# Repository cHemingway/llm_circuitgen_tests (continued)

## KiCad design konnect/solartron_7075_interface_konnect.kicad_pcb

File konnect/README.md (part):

# Konnect implementation

Solartron 7075 interface designed with [Konnect](https://github.com/mixelpixx/Konnect)
0.13.0, an MCP server that drives KiCad 10.0.6 (live IPC to the open editors,
with file-level tools for libraries and the schematic).

## Design

- 74 × 74 mm two-layer board. J1, a vertical DD-50 male (CAX DP-G-50P-ZC-YCLS,
  LCSC C54573066), sits on the bottom face, plugs into the meter's SKB socket
  and holds the board by its jackscrews. J2, a vertical USB-B (TE 5787834-1),
  sits on the top face.
- Meter side (GND_ISO): five SN74LVC165A shift registers read the 50-way
  interface's BCD and status lines through 100k pull-down networks. Two
  74LVC595A drive the command lines. An AMS1117-3.3 powers this side from a
  B0505S-1WR3 isolated DC-DC module.
- Isolation: six TLP2361 optocouplers carry the SPI-style links across a
  copper-free band about 4.8 mm wide. No net crosses the barrier.
- USB side (GND): RP2354A (internal flash), AP2112K-3.3, USBLC6-2SC6, BOOTSEL
  and RUN buttons, and an SWD header.
- Parts: KiCad's libraries, with LCSC numbers for every fitted part (the SWD
  header is optional and has none). KiCad has no DD-50, so its symbol and
  footprint are in the project library. The footprint follows the CAX
  part's drawing, checked against the DIN 41652 dimensions in Harting's
  catalogue. The project library also has a TLP2361 symbol with an
  inverting output.
- ERC: 0 errors, 0 warnings. DRC: 0 unconnected items and one cosmetic
  error: C17 pad 2 on the USB side, a ground pad with one thermal spoke
  where KiCad wants two, as in the first layout. The remaining items are
  warnings: footprints that differ from their library copies, silkscreen
  clipping, overlap and clearance, and a missing LCSC footprint field on the
  parity check.

## Review 1: pin swapping

The shift-register and resistor-array pins were re-assigned to untangle the
meter-side routing. The '165 inputs (D0–D7) are equivalent, as are the
'595 outputs (QA–QH) and the elements of the 100k arrays. The swaps were
therefore made both within each part and between identical parts.

- Each resistor array feeds one side of one '165. The 36 DVM outputs are
  taken in D-sub pin order, left to right. So the tracks run D-sub pin →
  array → '165 pin without crossing, almost all on the top layer.
- The '595 outputs follow the order of their D-sub pins. QA, the pin on the
  far side of the chip, takes the outermost signal.
- U16 D3..D0 keep the 0,0,1,1 signature. The SAMPLE line moved from U18
  QE/QD to QA/QC. The schematic's serial-link note now carries the full bit
  map that the firmware needs.
- The '165 LOAD and clock pins (1 and 2) escape to vias above each chip and
  join on two bottom-layer buses. Ground "pockets" (a bar and via over each
  array's ground pads, and vias for '165 pins 8 and 15) were placed before
  routing, so the input bus routes around them.
- The meter side was re-routed with Freerouting on top of those fixed
  pieces. The USB side was re-imported unchanged.

| Meter side | Before | After |
| --- | --- | --- |
| 36 '165 input nets | 1,343 mm, 53 vias | 781 mm, 7 vias |
| 13 '595 output nets | 157 mm, 7 vias | 118 mm, 1 via |
| 14 other nets (LOAD/SCK/MOSI/MISO, chain, +3V3_ISO) | 874 mm, 51 vias | 793 mm, 47 vias |
| All meter-side signals | 2,374 mm, 111 vias | 1,692 mm, 55 vias |
| GND_ISO stitching | 43 vias, 154 mm | 34 vias, 81 mm |

Whole board: 1,660 → 1,275 track segments and 201 → 136 vias.
`fab/routing_before_after.png` compares the meter-side routing before and after.

## Review 3: moving parts

The meter-side parts were moved, and the pins re-assigned again to suit.
This includes the swaps between parts offered in reply to review 2. The 36
DVM input tracks were laid out by a script, in one repeated pattern,
instead of by the autorouter.

- U16, the '165 with only four DVM inputs, moved from the middle of the row
  to the right-hand end. The nine '165 input sides that carry DVM lines now
  sit side by side, 11.08 mm per chip, which is twice the pitch of the
  D-sub's groups of four pins.
- Each array sits directly under its four D-sub pins, turned so that its
  signal pads face the connector. The tracks drop straight into the pads.
  On the way out, the outer two leave from the ends of the array, and the
  inner two run between its two rows of pads to the ends. Each '165 side
  takes two tracks from outside the chip and two from under the chip body.
- All 36 input tracks are on the top layer except DD-50 pin 36, which sits
  directly above pin 3. It uses one bottom-layer track and a via.
- The '165 decoupling caps moved to the top of each chip, between its two
  sets of input tracks, with a via to a bottom-layer +3V3_ISO spine. C29
  moved above the regulator to make room for U16. U19 turned round so that
  PRINT_LEVEL reaches its input directly.
- Both shift-register chains now run in board order. MOSI enters U18, U18
  feeds U17, and U17 loops back into U16. The '165 chain runs U16 → U15 →
  U14 → U12 → U13 → MISO. CMD_RATIO_N moved to U18 QD, next to the other
  U18 outputs. The serial-link note in the schematic has the new bit map.
- The script also placed:
  - the LOAD, SCK and OE buses on the bottom layer under both '595s, with a
    riser down the left of the D-sub;
  - SCK down a free channel under U15;
  - SIPO_CH1 under the '595 bodies;
  - a +3V3_ISO rail along the top edge and another along the opto row;
  - SIPO_LOOP down the right-hand side;
  - the '165 chain and MISO in a channel under the chips.
- Freerouting routed the rest: MOSI, the '595 outputs and the opto links.
  The USB side is unchanged.

| Meter side | Review 1 | Review 3 |
| --- | --- | --- |
| 36 '165 input nets | 781 mm, 7 vias | 655 mm, 1 via |
| 13 '595 output nets | 118 mm, 1 via | 96 mm, 0 vias |
| 14 other nets (LOAD/SCK/MOSI/MISO, chain, +3V3_ISO) | 793 mm, 47 vias | 807 mm, 35 vias |
| All meter-side signals | 1,692 mm, 55 vias | 1,558 mm, 36 vias |
| GND_ISO stitching | 34 vias, 81 mm | 27 vias, 65 mm |

Whole board: 1,275 → 958 track segments and 136 → 110 vias. DRC lost
Review 1's three starved thermals on the meter side (C24, C30 and C31). It
gained eight silkscreen overlap warnings, where the moved caps' reference
text overlaps the '165 outlines and C37's overlaps U19. Konnect has no tool
to move reference text. The positions file was regenerated; the BOM is
unchanged. `fab/routing_review3.png` compares the meter-side routing after
Review 1 and now.

| Path | Contents |
| --- | --- |
| `solartron_7075_interface_konnect.kicad_sch` / `.kicad_pcb` / `.kicad_pro` | KiCad project |
| `solartron.kicad_sym`, `solartron.pretty/` | Project symbols and footprints, including rect-pad copies of the stock footprints |
| `fab/` | Gerbers and drill files, JLCPCB BOM and positions, `schematic.pdf`, `pcb_layers.pdf`, DRC report, render, routing comparisons for reviews 1 and 3 |
| `CONVERSATION.md` | Session log and statistics |
| `stats.py`, `calls.csv` | Script for the statistics, and every API call with its category |
| `REVIEW_CONVERSATION.md` | Review log and statistics |
| `review_stats.py`, `review_calls.csv` | Script for the review statistics and log, and every review API call with its category |

## Notes on the tool

- Konnect's Specctra (Freerouting) export refuses roundrect pads, duplicate
  pad numbers and bottom-side footprints. Nearly every KiCad SMD footprint
  has roundrect pads. 15 stock footprints were therefore copied into the
  project library with rectangular pads. Routing-only variants were swapped
  in for the export and swapped back after the import: renumbered duplicate
  pads, and a front-side mirror of the bottom-mounted DD-50.
- The DSN export wrote each pin's rotation as an absolute angle, not relative
  to the footprint, so rotated parts had their pads turned twice and
  Freerouting reported 226 violations. The pin rotations were corrected in
  the scratch copy of the DSN. The session import then refused one part
  because the angles were written as 270 and −90, so those angles were
  normalised.
- Konnect has no tool to delete or move a via, or to delete a copper zone,
  and it deletes tracks one segment at a time. Its SES import also needs a
  board with no tracks, vias or zones. So re-routing after the pin swaps
  needed KiCad's own Edit ▸ Global Deletions, run in the GUI by screen
  control with the user's agreement. In Review 3 the same dialog was driven
  through the menu bar in the background. Each time, the whole board's
  copper was then re-imported through Konnect: the USB side unchanged, the
  meter side new.
- Konnect can move and rotate footprints but not their reference text, so
  silkscreen overlaps from moved parts stay as DRC warnings.
- KiCad's save rewrites the project's design rules and net classes, so the
  rules were re-applied before each DRC.
- The ground pours needed a lot of manual work: stitching vias, a
  ground-only Freerouting pass, a small grid router written in the
  scratchpad, and hand-placed thermal spokes.
- Freerouting 2.4.1 was downloaded with the user's permission and run both
  through Konnect and from the command line.

## Session statistics

`stats.py` reads the session transcript,
`~/.claude/projects/-Users-chris-repos-llm-circuitgen-tests/47e5c69c-808f-4cd7-8f0d-34a4d53529bd.jsonl`.
It takes everything before the export request (2026-10-15 18:44:30 UTC),
prints the tables in `CONVERSATION.md` and writes `calls.csv`. The export
itself ran in a resumed session, `3539381d-…`, whose file starts with a copy
of the original's later records. The original file is the complete record.

The review that followed ran in the same resumed session. `review_stats.py`
reads that session's transcript from the first review comment to the review
export request. It prints the review tables, writes `review_calls.csv` and,
with `--write-md`, writes `REVIEW_CONVERSATION.md`. The resumed session
writes no cost-state records, so the review figures come from the
transcript's per-response usage and tool timings, priced at the published
Opus 5.5 prices. `REVIEW_CONVERSATION.md` explains how each figure was
measured.

- **Totals** (tokens, API time, tool time and cost) come from the last
  `cost-state` record before the export request. API calls are the 520
  distinct assistant message ids; the usage-limit error message is not a
  call.
- **Active time** is measured from each typed message until the reply
  finished, giving four stretches.
  - Waiting for the user's answers to the two AskUserQuestion prompts (27 s
    and 2 min 14 s) is left out.
  - The 4 min stall between 20:52 and 20:57 on 2026-10-14 is left out. The
    session stopped after a tool result with no reply, and nothing ran
    until the user's "keep going".
  - Time waiting on background autorouter runs counts as active.
  - Each call is credited from its request (the record that triggered it)
    to the next call's request in the same stretch. The last call runs to
    the end of the stretch.
  - The 80 s compaction goes under Not attributable.
- **Categories** are set by call number in `stats.py`. Judgement calls:
  - The DD-50 footprint work (calls 43 and 68–71) is PCB. The search for a
    DD-50 drawing that came before it is Schematic & research, as part
    selection.
  - Everything from the schematic-to-PCB update (call 153) to the
    fabrication outputs (call 515) is PCB. That includes:
    - the rect-pad footprint copies, and pointing the schematic symbols at
      them;
    - the short replies to autorouter progress notifications;
    - the BOM export with the Gerbers.
  - Other covers:
    - creating the branch (call 1);
    - the two commits, the file send and the two summaries;
    - the connector status checks after "Continue" (calls 195–196).
- **Prices.** There are only two distinct cost-state snapshots, too few for
  a least-squares fit, so the published prices are used. They come from
  <https://platform.claude.com/docs/en/about-claude/pricing>, read on
  2026-10-15.
  - Claude Opus 5.5, per million tokens: $4 input, $5 for 5-minute cache
    writes, $8 for 1-hour cache writes, $0.20 for cache reads and $20 for
    output. The full 1M context is at standard prices.
  - Claude Haiku 5.5 (the web-tool helper): $0.10 input and $0.50 output for
    prompts up to 100k tokens, plus $10 per 1,000 web searches.

  Every cache write the transcript logs is a 1-hour write, and the 5-minute
  and 1-hour writes are priced separately per call. Checked against the
  snapshots:

  | Snapshot | Model | Reported | Published prices |
  | --- | --- | --- | --- |
  | 2026-10-14 21:05 | Opus 5.5 | $35.5377 | $35.5377 |
  | 2026-10-14 21:05 | Haiku 5.5 | $0.0777 | $0.0777 |
  | 2026-10-15 12:31 | Opus 5.5 | $112.1028 | $112.1034 |
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
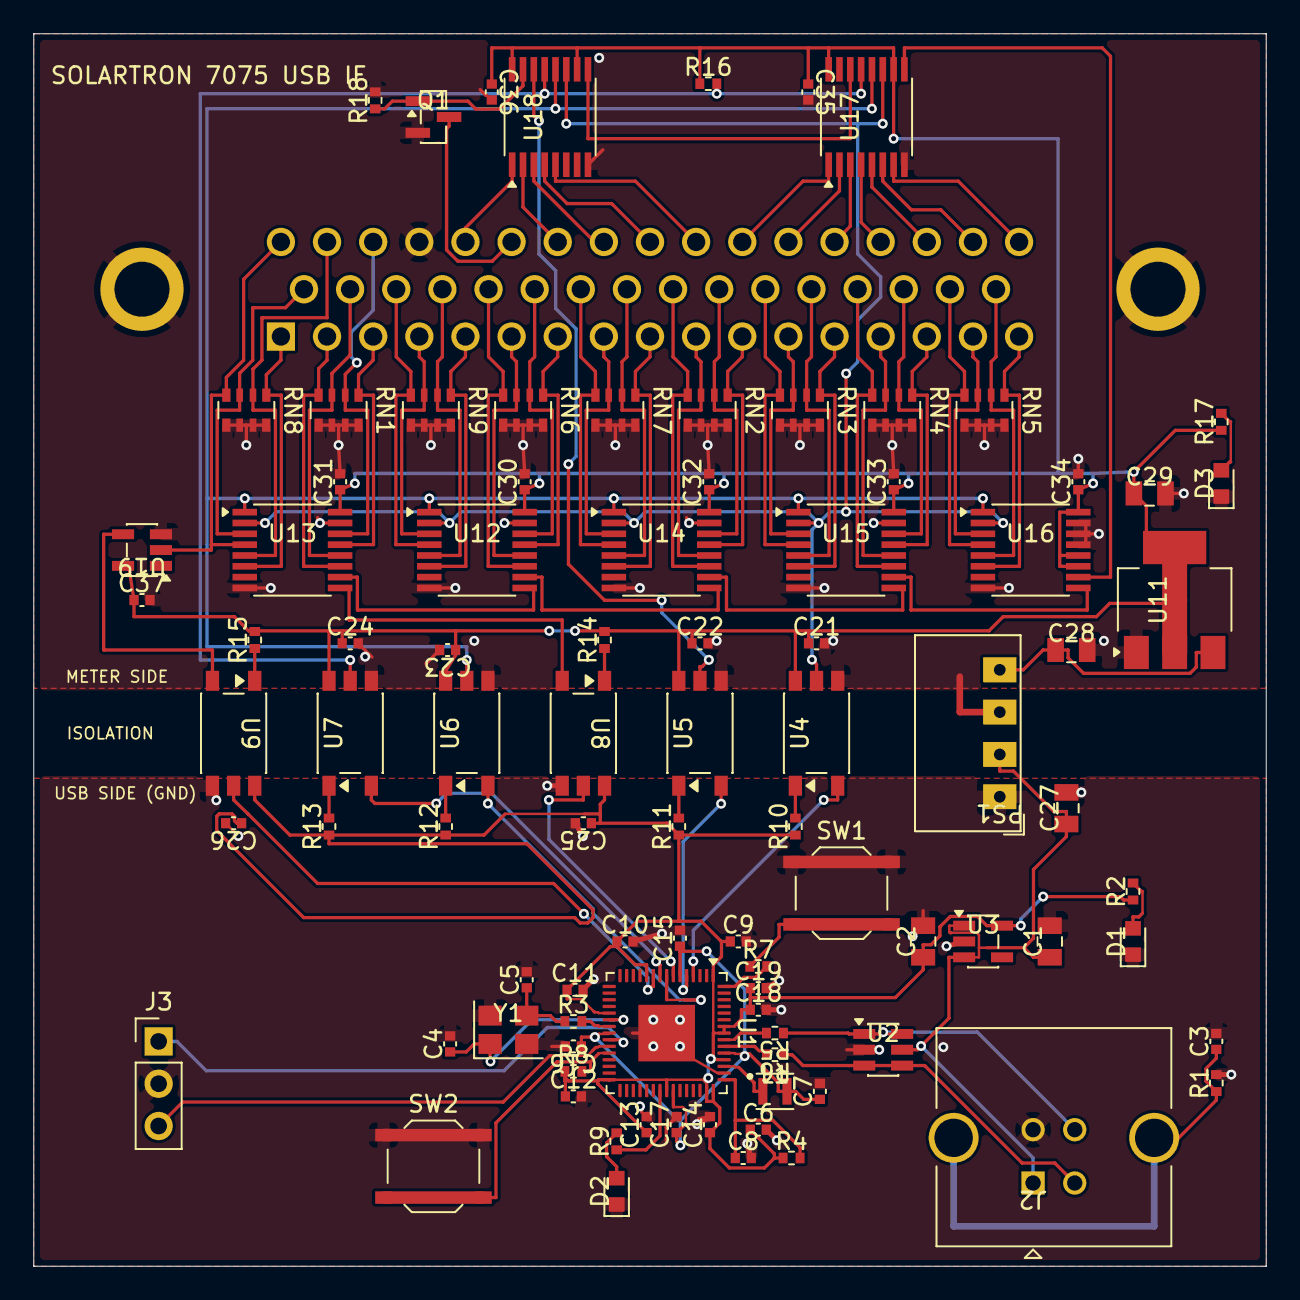
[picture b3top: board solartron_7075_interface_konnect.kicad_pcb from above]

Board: 2 copper layers, 74.0 x 74.0 mm, 93 parts (1 on the bottom side), 100 nets.

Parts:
C1, C2, C27, C28: 10uF; C_0805_2012Metric_RectPads
C3: 4.7nF; C_0402_1005Metric_RectPads
C4, C5: 15pF; C_0402_1005Metric_RectPads
C6, C7, C8: 4.7uF; C_0402_1005Metric_RectPads
C9, C10, C11, C12, C13, C14, C15, C16, C17, C18, C19, C21, C22, C23, C24, C25, C26, C30, C31, C32, C33, C34, C35, C36, C37: 100nF; C_0402_1005Metric_RectPads
C29: 22uF; C_0805_2012Metric_RectPads
D1, D2, D3: RED; LED_0603_1608Metric_RectPads
J1: DD-50 Male (Solartron SKB); DSUB-50_Pins_Vertical_P2.77x2.84mm_MountingHoles
J2: USB_B; USB_B_TE_5787834_Vertical_RectPads
J3: SWD; PinHeader_1x03_P2.54mm_Vertical
L1: 3.3uH; L_Murata_DFE201610P_RectPads
PS1: B0505S-1WR3; Converter_DCDC_Murata_CRE1xxxxxxSC_THT_RectPads
Q1: 2N7002; SOT-23_RectPads
R1: 1M; R_0402_1005Metric_RectPads
R2, R3, R7, R9, R17: 1k; R_0402_1005Metric_RectPads
R4: 33; R_0402_1005Metric_RectPads
R5, R6: 27; R_0402_1005Metric_RectPads
R8, R16: 10k; R_0402_1005Metric_RectPads
R10, R11, R12, R13, R14, R15: 470; R_0402_1005Metric_RectPads
R18: 100k; R_0402_1005Metric_RectPads
RN1, RN2, RN3, RN4, RN5, RN6, RN7, RN8, RN9: 100k; R_Array_Convex_4x0603
SW1: BOOTSEL; SW_Push_1P1T_XKB_TS-1187A
SW2: RUN; SW_Push_1P1T_XKB_TS-1187A
U1: RP2354A; QFN-60-1EP_7x7mm_P0.4mm_EP3.4x3.4mm
U2: USBLC6-2SC6; SOT-23-6_RectPads
U3: AP2112K-3.3; SOT-23-5_RectPads
U4, U5, U6, U7, U8, U9: TLP2361; SO-5-6_4.55x3.7mm_P1.27mm_RectPads
U11: AMS1117-3.3; SOT-223-3_TabPin2_RectPads
U12, U13, U14, U15, U16: SN74LVC165APWR; TSSOP-16_4.4x5mm_P0.65mm_RectPads
U17, U18: 74LVC595APW; TSSOP-16_4.4x5mm_P0.65mm_RectPads
U19: 74LVC1G17; SOT-23-5_RectPads
Y1: 12MHz; Crystal_SMD_3225-4Pin_3.2x2.5mm_RectPads

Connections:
+3V3: C2.1, C6.1, C9.1, C10.1, C11.1, C12.1, C13.1, C14.1, C18.1, C19.1, C25.1, C26.1, R2.1, R4.1, R8.1, R10.1, R11.1, R12.1, R13.1, U1.1, U1.11, U1.20, U1.30, U1.38, U1.44, U1.45, U1.49, U1.53, U1.54, U3.5, U8.6, U9.6
+3V3_ISO: C21.1, C22.1, C23.1, C24.1, C29.1, C30.1, C31.1, C32.1, C33.1, C34.1, C35.1, C36.1, C37.1, R14.2, R15.2, R16.1, R17.1, U4.6, U5.6, U6.6, U7.6, U11.2, U12.16, U13.16, U14.16, U15.16, U16.11, U16.12, U16.16, U17.10, U17.16, U18.10, U18.16, U19.5
+5V_ISO: C28.1, PS1.4, U11.3
/+1V1: C7.1, C15.1, C16.1, C17.1, L1.2, U1.6, U1.23, U1.39, U1.50
/BCD0_1: J1.25, RN7.2, U14.5
/BCD0_2: J1.24, RN7.4, U14.4
/BCD0_4: J1.23, RN6.2, U12.14
/BCD0_8: J1.22, RN6.4, U12.11
/BCD1_1: J1.21, RN9.2, U12.5
/BCD1_2: J1.20, RN9.4, U12.4
/BCD1_4: J1.19, RN1.3, U13.12
/BCD1_8: J1.18, RN8.3, U13.3
/BCD2_1: J1.17, RN5.1, U16.6
/BCD2_2: J1.16, RN5.3, U16.3
/BCD2_4: J1.15, RN4.1, U15.13
/BCD2_8: J1.14, RN4.3, U15.12
/BCD3_1: J1.13, RN3.1, U15.6
/BCD3_2: J1.12, RN3.3, U15.3
/BCD3_4: J1.11, RN2.1, U14.13
/BCD3_8: J1.10, RN2.3, U14.12
/BCD4_1: J1.9, RN7.1, U14.6
/BCD4_2: J1.8, RN7.3, U14.3
/BCD4_4: J1.7, RN6.1, U12.13
/BCD4_8: J1.6, RN6.3, U12.12
/BCD5_1: J1.5, RN9.1, U12.6
/BCD5_2: J1.4, RN9.3, U12.3
/BCD5_4: J1.3, RN1.1, U13.13
/BCD5_8: J1.2, RN1.4, U13.11
/BCD6_1: J1.1, RN8.1, U13.6
/CMD_AUTORANGE_INH: J1.47, U17.4
/CMD_FN_42: J1.42, U18.4
/CMD_FN_43: J1.43, U18.5
/CMD_FPL_N: J1.38, U18.1
/CMD_INT_1: J1.46, U17.3
/CMD_INT_2: J1.45, U17.2
/CMD_INT_4: J1.44, U17.1
/CMD_RATIO_N: J1.41, U18.3
/CMD_RNG_1: J1.48, U17.5
/CMD_RNG_2: J1.49, U17.6
/CMD_RNG_4: J1.50, U17.7
/CMD_SAMPLE_CONTACT: J1.39, Q1.3
/CMD_SAMPLE_PULSE: J1.40, U18.2
/DATA_CAN_CHANGE: J1.35, RN8.2, U13.5
/FN_OUT_28: J1.28, RN3.4, U15.4
/FN_OUT_29: J1.29, RN3.2, U15.5
/ISO_LOAD: U6.5, U12.1, U13.1, U14.1, U15.1, U16.1, U17.12, U18.12
/ISO_MISO: U8.3, U13.9
/ISO_MOSI: U5.5, U18.14
/ISO_OE_N: R16.2, U7.5, U17.13, U18.13
/ISO_PRINT_DRV: U9.3, U19.4
/ISO_SCK: U4.5, U12.2, U13.2, U14.2, U15.2, U16.2, U17.11, U18.11
/LED_STAT: R9.1, U1.37
/MISO: U1.7, U8.5
/OPTO_LOAD: U1.8, U6.3
/OPTO_MOSI: U1.5, U5.3
/OPTO_OE_N: U1.9, U7.3
/OPTO_SCK: U1.4, U4.3
/OVERLOAD: J1.36, RN1.2, U13.14
/PISO_CH1: U12.9, U13.10
/PISO_CH2: U12.10, U14.9
/PISO_CH3: U14.10, U15.9
/PISO_CH4: U15.10, U16.9
/POL_NEG: J1.27, RN2.2, U14.14
/POL_POS: J1.26, RN2.4, U14.11
/PRINT: U1.10, U9.5
/PRINT_LEVEL: J1.34, RN8.4, U13.4, U19.2
/PRINT_PULSE: J1.33, RN5.2, U16.5
/RNG_OUT_1: J1.32, RN5.4, U16.4
/RNG_OUT_2: J1.31, RN4.2, U15.14
/RNG_OUT_4: J1.30, RN4.4, U15.11
/SAMPLE_CONTACT_DRV: Q1.1, R18.1, U18.15
/SIPO_CH1: U17.14, U18.9
/SIPO_LOOP: U16.10, U17.9
/SWCLK: J3.1, U1.24
/SWDIO: J3.3, U1.25
/USB_CONN_DM: J2.2, R6.1, U2.3, U2.4
/USB_CONN_DP: J2.3, R5.1, U2.1, U2.6
/USB_DM: R6.2, U1.51
/USB_DP: R5.2, U1.52
/USB_SHIELD: C3.1, J2.SH, R1.1
/VREG_AVDD: C8.1, R4.2, U1.46
/VREG_LX: L1.1, U1.48
/XIN: C4.1, U1.21, Y1.1
/XTAL_OUT: C5.1, R3.1, Y1.3
GND: C1.2, C2.2, C3.2, C4.2, C5.2, C6.2, C7.2, C8.2, C9.2, C10.2, C11.2, C12.2, C13.2, C14.2, C15.2, C16.2, C17.2, C18.2, C19.2, C25.2, C26.2, C27.2, D1.1, D2.1, J2.4, J3.2, PS1.1, R1.2, SW1.1, SW2.1, U1.47, U1.61, U2.2, U3.2, U8.4, U9.4, Y1.2, Y1.4
GND_ISO: C21.2, C22.2, C23.2, C24.2, C28.2, C29.2, C30.2, C31.2, C32.2, C33.2, C34.2, C35.2, C36.2, C37.2, D3.1, J1.37, J1.SH, PS1.3, Q1.2, R18.2, RN1.5, RN1.6, RN1.7, RN1.8, RN2.5, RN2.6, RN2.7, RN2.8, RN3.5, RN3.6, RN3.7, RN3.8, RN4.5, RN4.6, RN4.7, RN4.8, RN5.5, RN5.6, RN5.7, RN5.8, RN6.5, RN6.6, RN6.7, RN6.8, RN7.5, RN7.6, RN7.7, RN7.8, RN8.5, RN8.6, RN8.7, RN8.8, RN9.5, RN9.6, RN9.7, RN9.8, U4.4, U5.4, U6.4, U7.4, U11.1, U12.8, U12.15, U13.8, U13.15, U14.8, U14.15, U15.8, U15.15, U16.8, U16.13, U16.14, U16.15, U17.8, U18.8, U19.3
unnamed: D1.2, R2.2
unnamed: D2.2, R9.2
unnamed: D3.2, R17.2
unnamed: R7.1, SW1.2
unnamed: R8.2, SW2.2, U1.26
unnamed: R3.2, U1.22
unnamed: R7.2, U1.60
unnamed: R10.2, U4.1
unnamed: R11.2, U5.1
unnamed: R12.2, U6.1
unnamed: R13.2, U7.1
unnamed: R14.1, U8.1
unnamed: R15.1, U9.1
VBUS: C1.1, C27.1, J2.1, PS1.2, U2.5, U3.1, U3.3

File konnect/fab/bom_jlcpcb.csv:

"Comment","Designator","Footprint","LCSC Part #","MPN","Manufacturer","Quantity"
"10uF","C1,C2,C27,C28","solartron:C_0805_2012Metric_RectPads","C15850","CL21A106KAYNNNE","Samsung Electro-Mechanics","4"
"4.7nF","C3","solartron:C_0402_1005Metric_RectPads","C1538","0402B472K500NT","FH (Guangdong Fenghua)","1"
"15pF","C4,C5","solartron:C_0402_1005Metric_RectPads","C1548","0402CG150J500NT","FH (Guangdong Fenghua)","2"
"4.7uF","C6-C8","solartron:C_0402_1005Metric_RectPads","C23733","CL05A475MP5NRNC","Samsung Electro-Mechanics","3"
"100nF","C9-C19,C21-C26,C30-C37","solartron:C_0402_1005Metric_RectPads","C1525","CL05B104KO5NNNC","Samsung Electro-Mechanics","25"
"22uF","C29","solartron:C_0805_2012Metric_RectPads","C45783","CL21A226MAQNNNE","Samsung Electro-Mechanics","1"
"RED","D1-D3","solartron:LED_0603_1608Metric_RectPads","C2286","KT-0603R","Hubei KENTO Elec","3"
"DD-50 Male (Solartron SKB)","J1","solartron:DSUB-50_Pins_Vertical_P2.77x2.84mm_MountingHoles","C54573066","DP-G-50P-ZC-YCLS","CAX (Zhejiang Chuangdu)","1"
"USB_B","J2","solartron:USB_B_TE_5787834_Vertical_RectPads","C592900","5787834-1","TE Connectivity","1"
"SWD","J3","Connector_PinHeader_2.54mm:PinHeader_1x03_P2.54mm_Vertical","","2.54mm 1x3 pin header (fit by hand / optional)","","1"
"3.3uH","L1","solartron:L_Murata_DFE201610P_RectPads","C42411119","AOTA-B201610S3R3-101-T","Abracon","1"
"B0505S-1WR3","PS1","solartron:Converter_DCDC_Murata_CRE1xxxxxxSC_THT_RectPads","C7465178","B0505S-1WR3","EVISUN","1"
"2N7002","Q1","solartron:SOT-23_RectPads","C8545","2N7002","Jiangsu Changjing (CJ)","1"
"1M","R1","solartron:R_0402_1005Metric_RectPads","C26083","0402WGF1004TCE","UNI-ROYAL","1"
"1k","R2,R3,R7,R9,R17","solartron:R_0402_1005Metric_RectPads","C11702","0402WGF1001TCE","UNI-ROYAL","5"
"33","R4","solartron:R_0402_1005Metric_RectPads","C25105","0402WGF330JTCE","UNI-ROYAL","1"
"27","R5,R6","solartron:R_0402_1005Metric_RectPads","C25100","0402WGF270JTCE","UNI-ROYAL","2"
"10k","R8,R16","solartron:R_0402_1005Metric_RectPads","C25744","0402WGF1002TCE","UNI-ROYAL","2"
"470","R10-R15","solartron:R_0402_1005Metric_RectPads","C25117","0402WGF4700TCE","UNI-ROYAL","6"
"100k","R18","solartron:R_0402_1005Metric_RectPads","C25741","0402WGF1003TCE","UNI-ROYAL","1"
"100k","RN1-RN9","Resistor_SMD:R_Array_Convex_4x0603","C1996","4D03WGJ0104T5E","UNI-ROYAL","9"
"BOOTSEL","SW1","Button_Switch_SMD:SW_Push_1P1T_XKB_TS-1187A","C318884","TS-1187A-B-A-B","XKB Connection","1"
"RUN","SW2","Button_Switch_SMD:SW_Push_1P1T_XKB_TS-1187A","C318884","TS-1187A-B-A-B","XKB Connection","1"
"RP2354A","U1","Package_DFN_QFN:QFN-60-1EP_7x7mm_P0.4mm_EP3.4x3.4mm","C41378174","RP2354A","Raspberry Pi","1"
"USBLC6-2SC6","U2","solartron:SOT-23-6_RectPads","C7519","USBLC6-2SC6","STMicroelectronics","1"
"AP2112K-3.3","U3","solartron:SOT-23-5_RectPads","C51118","AP2112K-3.3TRG1","Diodes Incorporated","1"
"TLP2361","U4-U9","solartron:SO-5-6_4.55x3.7mm_P1.27mm_RectPads","C107626","TLP2361(TPL,E","Toshiba","6"
"AMS1117-3.3","U11","solartron:SOT-223-3_TabPin2_RectPads","C6186","AMS1117-3.3","Advanced Monolithic Systems","1"
"SN74LVC165APWR","U12-U16","solartron:TSSOP-16_4.4x5mm_P0.65mm_RectPads","C41558098","SN74LVC165APWR","Texas Instruments","5"
"74LVC595APW","U17,U18","solartron:TSSOP-16_4.4x5mm_P0.65mm_RectPads","C426713","74LVC595APW,118","Nexperia","2"
"74LVC1G17","U19","solartron:SOT-23-5_RectPads","C7836","SN74LVC1G17DBVR","Texas Instruments","1"
"12MHz","Y1","solartron:Crystal_SMD_3225-4Pin_3.2x2.5mm_RectPads","C20625731","ABM8-272-T3","Abracon","1"

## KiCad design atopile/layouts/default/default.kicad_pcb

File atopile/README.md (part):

# Solartron 7075 USB interface (atopile)

An RP2354A USB interface that plugs straight into the 50-way SKB socket of a
Solartron 7075 DVM fitted with the 70754 Parallel BCD Interface Unit (service
manual, section 9). Every signal to and from the meter crosses an optical
isolation barrier, so USB ground noise never reaches the meter's ground. SKB
pin 37 is the meter's earth and logic 0.

Designed with atopile 0.15.9 (`ato build`). The parts come from atopile's
package library where it had them, and from LCSC otherwise.

## Architecture

```
 USB side (GND)                         |  DVM side (GND_ISO)
                                        |
 USB-B (vertical) -> 500 mA PTC, USBLC6 |
   +5V --+--> TLV75901 -> +3V3          |
         +--> IB0505LS-1WR3 ===========>|==> +5V_ISO (regulated, 1.5 kV)
                                        |
 RP2354A  GPIO18 SCK  --> TLP2361 ======|==> SCK_ISO   -> 5x 74HCT165 CP, 2x 74HCT595 SHCP
          GPIO19 MOSI --> TLP2361 ======|==> MOSI_ISO  -> first 74HCT595 DS
          GPIO17 LATCH--> TLP2361 ======|==> LATCH_ISO -> 74HCT165 /PL, 74HCT595 STCP
          GPIO20 OE_N --> TLP2361 ======|==> OE_N_ISO  -> 74HCT595 /OE (10 k pull-up)
          GPIO16 MISO <-- TLP2361 ======|<== first 74HCT165 Q7
          GPIO21 DRDY <-- TLP2361 ======|<== 74AHCT1G125 <- SKB 34 (PRINT level)
                                        |
                                        |   SKB 1-36  (BCD, polarity, function, range,
                                        |              print, data-can-change, overload)
                                        |              -> 5x 74HCT165 (40-bit chain)
                                        |   SKB 38, 40-50 <- 2x 74HCT595 (16-bit chain)
                                        |   SKB 39 (contact SAMPLE) <- 2N7002 to pin 37
```

* Only six logic signals cross the barrier. Each goes through a Toshiba
  TLP2361 optocoupler (15 MBd, 80 ns max delay). Every channel is
  non-inverting: the MCU or HCT output sinks the LED cathode, and the anode
  is fed from 330 Ω (3.3 V side) or 680 Ω (5 V side), about 4.5 mA.
* The DVM side uses HCT logic at 5 V because the 7075's outputs are TTL
  levels: a '1' is +2.4 to +6 V from a 6 kΩ source. The 74HCT595 outputs
  sink 6 mA at under 0.33 V, which meets the 7075 input spec of under 0.5 V
  at 5 mA.
* **Safe at reset.** While the MCU is in reset or not yet configured, its
  GPIOs are Hi-Z, so the opto LEDs are off and every isolated line idles
  high. That keeps `OE_N_ISO` high, so the 595 outputs stay Hi-Z and the
  meter's command inputs sit at its own pull-ups, exactly as if nothing were
  connected. Manual §9, diagram 9.2 (70754 board 2) confirms the pull-ups:
  * every command input has 4.7 kΩ to +5 V into 74-series TTL, so Hi-Z reads
    '1' = inactive (no lockout, no ratio, DC, 10 s, autorange; the manual's
    "REMOTE with nothing connected" state)
  * CONTACT SAMPLE has 2.2 kΩ to +5 V, so with the MOSFET off there is no
    sample
  * PULSE SAMPLE is AC-coupled (47 kΩ + 22 nF), so only a rising edge
    triggers it
* The four spare 74HCT165 inputs are tied to two 1s and two 0s, so firmware
  can detect a broken link or a missing isolated supply. Their places in the
  frame are in the read-frame table below.

## Firmware interface

SPI0 runs in mode 0 at 1 MHz or less. The limit comes from the round trip
through two optos, about 200 ns. **LATCH must be driven as a plain GPIO**, not
as the SPI chip select, because the 74HCT165s are held in load mode while it
is low. Set GPIO17–20 to 8 mA drive.

One transaction:

1. Pulse LATCH (GPIO17) low for at least 1 µs, then return it high. The
   rising edge does two things: the 165s capture the DVM outputs, and the
   595s present the command word that was shifted in last time.
2. Exchange 5 bytes over SPI. MOSI = `00 00 00 CMD_HI CMD_LO`. MISO = 5
   status bytes.
3. To apply the new command now, pulse LATCH again. Otherwise it is applied
   at the next transaction.
4. After the first valid command has been latched, drive OE_N (GPIO20) low.
   That command must have the PULSE SAMPLE bit = 0. PULSE SAMPLE is
   AC-coupled in the meter, so enabling the outputs with that bit = 1 would be
   a rising edge and would trigger a sample.

DRDY (GPIO21) follows SKB pin 34, PRINT level. It goes high when a reading is
complete and the outputs have been updated.

<!-- BEGIN bit maps: generated by scripts/pin_swap.py -->
### Read frame (MISO, MSB first)

Each cell gives the SKB pin and its meaning. `1`/`0` are the link-check
constants: firmware should check them on every read.

| Byte | bit7 | bit6 | bit5 | bit4 | bit3 | bit2 | bit1 | bit0 |
|---|---|---|---|---|---|---|---|---|
| 0 | 1 1×10⁶ | 34 PRINT level | 2 8×10⁵ | 18 8×10¹ | `0` | `1` | `0` | 35 DATA CAN CHANGE |
| 1 | 19 4×10¹ | 3 4×10⁵ | 36 OVERLOAD | 20 2×10¹ | 22 8×10⁰ | 5 1×10⁵ | 21 1×10¹ | 4 2×10⁵ |
| 2 | 6 8×10⁴ | 23 4×10⁰ | 7 4×10⁴ | 24 2×10⁰ | `1` | 9 1×10⁴ | 25 1×10⁰ | 8 2×10⁴ |
| 3 | 11 4×10³ | 27 −ve | 10 8×10³ | 26 +ve | 28 function A | 12 2×10³ | 29 function B | 13 1×10³ |
| 4 | 32 range (1) | 14 8×10² | 31 range (2) | 30 range (4) | 15 4×10² | 33 PRINT pulse | 16 2×10² | 17 1×10² |

### Command word (MOSI bytes 3–4, CMD_HI = bits 15–8)

| Bit | SKB pin | Signal (manual §9) |
|---|---|---|
| 0 | 38 | FRONT PANEL LOCKOUT (0 = locked out) |
| 1 | 39 | CONTACT SAMPLE (1 = MOSFET closes 39 to 37) |
| 2 | 43 | FUNCTION B |
| 3 | 42 | FUNCTION A |
| 4 | 44 | Integration time (4) |
| 5 | 41 | RATIO (0 = ratio) |
| 6 | 40 | PULSE SAMPLE (pulse high for more than 100 µs) |
| 7 | – | unused |
| 8 | 45 | Integration time (2) |
| 9 | 49 | Range (2) |
| 10 | 50 | Range (4) |
| 11 | 48 | Range (1) |
| 12 | 47 | AUTORANGE (1 = autorange inhibited, use the commanded range) |
| 13 | 46 | Integration time (1) |
| 14 | – | unused |
| 15 | – | unused |

* FUNCTION, read as (43, 42): 11 = DC, 01 = AC, 10 = Ω, 00 = CHECK.
* Integration time, read as (44, 45, 46) = (4)(2)(1): 011 = 1 ms, 100 = 20 ms,
  101 = 100 ms, 110 = 1 s, 111 = 10 s.
* Range, read as (50, 49, 48) = (4)(2)(1): 000 = 1000 V / 10 MΩ … 101 = 10 mV /
  100 Ω, 110 = auto / 10 Ω, 111 = auto.
<!-- END bit maps -->

Commands only take effect while the meter is in REMOTE. That means either the
REMOTE button is pressed, or the FRONT PANEL LOCKOUT bit = 0.

## Board

* 78 × 60 mm rectangle, 4 layers, 1.6 mm. It sits flat on the back of the
  meter and has no mounting holes.
* **Stack-up** (JLCPCB's standard 7628 build, nominal values):

  | Layer | Use | Copper | Dielectric below |
  |---|---|---|---|
  | F.Cu | signals, all parts except the DD-50 | 35 µm | 0.2 mm 7628 prepreg |
  | In1.Cu | ground planes: GND (USB half), GND_ISO (DVM half) | 17.5 µm | 1.065 mm core |
  | In2.Cu | supply planes: +3V3 (USB half), +5V_ISO (DVM half) | 17.5 µm | 0.2 mm 7628 prepreg |
  | B.Cu | signals, DD-50 | 35 µm | |

* **Bottom face:** Amphenol DD50P364TXLF, a vertical PCB-mount DD-50 plug. It
  mates with SKB and is held by 4-40 jackscrews through its 3.1 mm flange
  holes. The top face is kept clear within 4 mm of each jackscrew for the
  screw heads.
* **Top face:**
  * the vertical USB-B (SHOU HAN BF 180) and the rest of the components
  * isolation barrier along the board centreline: a 3.2 mm keep-out on all
    four layers with no tracks, vias or copper, crossed only by the six
    TLP2361s and the SIP DC-DC. The inner planes stop 1.9 mm either side of
    the centreline, so the planes on the two sides are 3.8 mm apart.
  * no pours on the outer layers; they are left for signals
* `scripts/place_components.py` produces the initial placement, the layer
  stack and the zones, using atopile's own `PCB_Transformer`.
  `scripts/check_layout.py` checks:
  * every pad is inside the outline
  * no footprints overlap
  * all USB-side pads are north of the barrier and all DVM-side pads south
  * the jackscrew keep-outs are clear
* The TLV75901 library module arrives pre-routed. The placement script moves
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
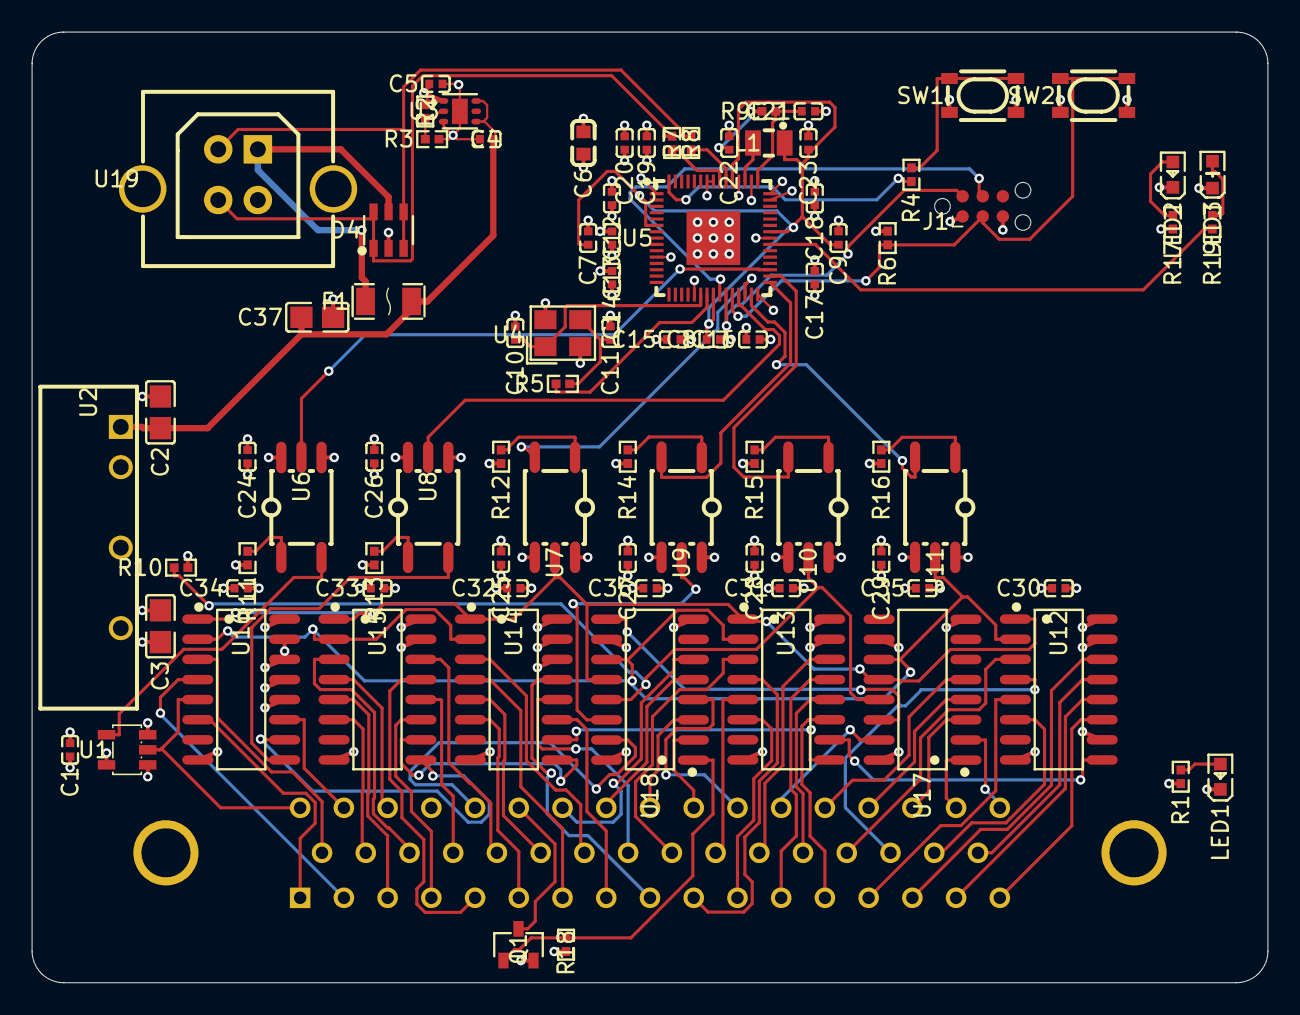
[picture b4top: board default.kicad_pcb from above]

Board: 4 copper layers, 78.0 x 60.0 mm, 86 parts (1 on the bottom side), 99 nets.

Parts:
C1, C7, C8, C9, C12, C13, C14, C15, C16, C17, C18, C19, C20, C24, C25, C26, C27, C28, C29, C30, C31, C32, C33, C34, C35, C36: 100nF ±10%; C0402
C2: 4.7µF ±10%; C0805
C3, C37: 10µF ±10%; C0805
C4, C5: 1µF ±10%; C0402
C6: 10µF ±10%; C0603
C10, C11: 15pF ±5%; C0402
C21, C22, C23: 4.7µF ±20%; C0402
CN1: CONN-TH_50P-P2.76_DD50P364TXLF
D4: SOT-23-6_L2.9-W1.6-P0.95-LS2.8-BL
F1: F1206
J1: Tag-Connect_TC2030-IDC-NL_2x03_P1.27mm_Vertical
L1: IND-SMD_L2.0-W1.6_AOTA-B201610S3R3-101-T
LED1, LED2: LED0603-RD
LED3: LED0603-R-RD
Q1: SOT-23-3_L2.9-W1.3-P1.90-LS2.4-BR
R1: 3.3kΩ ±1%; R0402
R2, R18: 100kΩ ±1%; R0402
R3: 20kΩ ±1%; R0402
R4, R5: 1kΩ ±1%; R0402
R6, R10: 10kΩ ±1%; R0402
R7, R8: 27Ω ±1%; R0402
R9: 33Ω ±1%; R0402
R11, R13: 680Ω ±1%; R0402
R12, R14, R15, R16: 330Ω ±1%; R0402
R17, R19: 1.5kΩ ±1%; R0402
SW1, SW2: KEY-SMD_4P-L4.2-W3.2-P2.20-LS4.6
U1: SOT-23-5_L3.0-W1.7-P0.95-LS2.8-BR
U2: PWRM-TH_BXXXXLS-1WR3
U3: WSON-6_L2.0-W2.0-P0.65-TL-EP
U4: CRYSTAL-SMD_4P-L3.2-W2.5-BL
U5: QFN-60_L7.0-W7.0-P0.40-TL-EP3.4
U6, U7, U8, U9, U10, U11: OPTO-SMD-5_L3.7-W4.6-P1.27-LS7.0-BR
U12, U13, U14, U15, U16, U17, U18: SOIC-16_L9.9-W3.9-P1.27-LS6.0-BL
U19: USB-B-TH_921-111A1010Y10201

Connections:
+1V1: C7.1, C8.1, C9.1, C23.1, L1.2, U5.6, U5.23, U5.39, U5.50
+3V3: C5.1, C6.1, C12.1, C13.1, C14.1, C15.1, C16.1, C17.1, C18.1, C19.1, C20.1, C22.1, C24.1, C26.1, J1.1, R2.1, R6.2, R9.1, R12.1, R14.1, R15.1, R16.1, R17.1, U3.1, U5.1, U5.11, U5.20, U5.30, U5.38, U5.44, U5.45, U5.49, U5.53, U5.54, U6.6, U8.6
+5V: C2.1, C4.1, C37.1, F1.2, U2.1, U3.4, U3.6
+5V_ISO: C1.1, C3.1, C25.1, C27.1, C28.1, C29.1, C30.1, C31.1, C32.1, C33.1, C34.1, C35.1, C36.1, R1.1, R10.2, R11.1, R13.1, U1.5, U2.6, U7.6, U9.6, U10.6, U11.6, U12.16, U13.16, U14.14, U14.16, U15.16, U16.13, U16.16, U17.10, U17.16, U18.10, U18.16
AN: R11.2, U6.1
BOOTSEL_SW: R4.2, SW1.1, SW1.2
CLK: J1.4, U5.24
DATA_N: D4.3, D4.4, R8.1, U19.2
DATA_P: D4.1, D4.6, R7.1, U19.3
DIO: J1.2, U5.25
DRDY: U5.33, U6.5
DRDY_ISO: U1.4, U6.3
GND: C2.2, C4.2, C5.2, C6.2, C7.2, C8.2, C9.2, C10.2, C11.2, C12.2, C13.2, C14.2, C15.2, C16.2, C17.2, C18.2, C19.2, C20.2, C21.2, C22.2, C23.2, C24.2, C26.2, C37.2, D4.2, J1.5, LED2.1, LED3.2, R3.2, SW1.3, SW1.4, SW2.3, SW2.4, U2.2, U3.3, U3.7, U4.2, U4.4, U5.47, U5.61, U6.4, U8.4, U19.4, U19.5, U19.6
GND_ISO: C1.2, C3.2, C25.2, C27.2, C28.2, C29.2, C30.2, C31.2, C32.2, C33.2, C34.2, C35.2, C36.2, CN1.37, CN1.S1, CN1.S2, LED1.1, Q1.2, R18.2, U1.1, U1.3, U2.4, U7.4, U9.4, U10.4, U11.4, U12.8, U12.10, U12.15, U13.8, U13.15, U14.8, U14.15, U15.8, U15.15, U16.8, U16.12, U16.14, U16.15, U17.8, U18.8
LATCH: U5.28, U7.3
LATCH_ISO: U7.5, U12.1, U13.1, U14.1, U15.1, U16.1, U17.12, U18.12
LDO_FB: R2.2, R3.1, U3.2
LED_ISO_A: LED1.2, R1.2
LED_PWR_A: LED2.2, R17.2
LED_STATUS_A: LED3.1, R19.2
MISO: U5.27, U8.5
MISO_ISO: U8.3, U16.9
MOSI: U5.31, U9.3
MOSI_ISO: U9.5, U18.14
N_RESET: J1.3, R6.1, SW2.1, SW2.2, U5.26
OE_N: U5.32, U10.3
OE_N_ISO: R10.1, U10.5, U17.13, U18.13
QSPI_SS: R4.1, U5.60
SAMPLE_CONTACT_GATE: Q1.1, R18.1, U18.1
SCK: U5.29, U11.3
SCK_ISO: U11.5, U12.2, U13.2, U14.2, U15.2, U16.2, U17.11, U18.11
SI_CHAIN_1: U15.9, U16.10
SI_CHAIN_2: U14.9, U15.10
SI_CHAIN_3: U13.9, U14.10
SI_CHAIN_4: U12.9, U13.10
SKB01_D6_1: CN1.1, U16.6
SKB02_D5_8: CN1.2, U16.4
SKB03_D5_4: CN1.3, U15.5
SKB04_D5_2: CN1.4, U15.11
SKB05_D5_1: CN1.5, U15.13
SKB06_D4_8: CN1.6, U14.6
SKB07_D4_4: CN1.7, U14.4
SKB08_D4_2: CN1.8, U14.11
SKB09_D4_1: CN1.9, U14.13
SKB10_D3_8: CN1.10, U13.4
SKB11_D3_4: CN1.11, U13.6
SKB12_D3_2: CN1.12, U13.13
SKB13_D3_1: CN1.13, U13.11
SKB14_D2_8: CN1.14, U12.5
SKB15_D2_4: CN1.15, U12.14
SKB16_D2_2: CN1.16, U12.12
SKB17_D2_1: CN1.17, U12.11
SKB18_D1_8: CN1.18, U16.3
SKB19_D1_4: CN1.19, U15.6
SKB20_D1_2: CN1.20, U15.3
SKB21_D1_1: CN1.21, U15.12
SKB22_D0_8: CN1.22, U15.14
SKB23_D0_4: CN1.23, U14.5
SKB24_D0_2: CN1.24, U14.3
SKB25_D0_1: CN1.25, U14.12
SKB26_POL_POS: CN1.26, U13.3
SKB27_POL_NEG: CN1.27, U13.5
SKB28_FUNC_OUT_A: CN1.28, U13.14
SKB29_FUNC_OUT_B: CN1.29, U13.12
SKB30_RANGE_OUT_4: CN1.30, U12.3
SKB31_RANGE_OUT_2: CN1.31, U12.4
SKB32_RANGE_OUT_1: CN1.32, U12.6
SKB33_PRINT_PULSE: CN1.33, U12.13
SKB34_PRINT_LEVEL: CN1.34, U1.2, U16.5
SKB35_DATA_CAN_CHANGE: CN1.35, U16.11
SKB36_OVERLOAD: CN1.36, U15.4
SKB38_LOCKOUT: CN1.38, U18.15
SKB39_SAMPLE_CONTACT: CN1.39, Q1.3
SKB40_SAMPLE_PULSE: CN1.40, U18.6
SKB41_RATIO: CN1.41, U18.5
SKB42_FUNC_CMD_A: CN1.42, U18.3
SKB43_FUNC_CMD_B: CN1.43, U18.2
SKB44_INT_TIME_4: CN1.44, U18.4
SKB45_INT_TIME_2: CN1.45, U17.15
SKB46_INT_TIME_1: CN1.46, U17.5
SKB47_AUTORANGE: CN1.47, U17.4
SKB48_RANGE_CMD_1: CN1.48, U17.3
SKB49_RANGE_CMD_2: CN1.49, U17.1
SKB50_RANGE_CMD_4: CN1.50, U17.2
SO_CHAIN_1: U17.14, U18.9
STATUS_LED: R19.1, U5.37
USB_DM: R8.2, U5.51
USB_DP: R7.2, U5.52
VBUS: D4.5, F1.1, U19.1
VREG_AVDD: C21.1, R9.2, U5.46
VREG_LX: L1.1, U5.48
XIN: C10.1, U4.1, U5.21
XOUT: R5.1, U5.22
XTAL_OUT: C11.1, R5.2, U4.3
opto_latch-AN: R12.2, U7.1
opto_miso-AN: R13.2, U8.1
opto_mosi-AN: R14.2, U9.1
opto_oe_n-AN: R15.2, U10.1
opto_sck-AN: R16.2, U11.1

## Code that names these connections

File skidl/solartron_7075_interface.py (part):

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# Isolated / meter side
iso_9v = power_net("ISO_+9V")
iso_5v = power_net("ISO_+5V")
iso_gnd = power_net("ISO_GND")  # = Solartron pin 37 "EARTH / Logic 0"

# MCU <-> optocoupler (host side)
mcu_sclk, mcu_mosi, mcu_miso, mcu_latch, mcu_oe_n = (
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# Inputs to the meter (TTL, '1' = +2.4..+5 V, '0' must sink 5 mA)
METER_IN = {
    "LOCKOUT_N": 38,      # 0 = front panel lockout (forces REMOTE)
    "SAMPLE_CONTACT": 39,  # contact closure to pin 37 starts a reading
    "SAMPLE_PULSE": 40,   # +3..+8 V pulse > 100 us starts a reading
    "RATIO_N": 41,        # 0 = ratio
    "FUNC_CMD_42": 42,    # function command (43,42): 11 DC, 01 AC, 10 ohm, 00 check
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        c[1, 2] += n, gnd

    # USB with 27R series resistors (RP2350 has the D+ pull-up on chip)
    for pin, net in (("USB_DP", usb_dp), ("USB_DM", usb_dm)):
        r = R("27", "0402")
        mcu_side = Net(f"MCU_{pin}")
        r[1, 2] += net, mcu_side
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    u["SWDIO"] += swdio
    swd[1, 2, 3] += swclk, gnd, swdio

    # Isolated link on GPIO20-24 (one contiguous run of pins facing the
    # optocouplers): GPIO20/22/23 = SPI0 RX/SCK/TX, GPIO21 = LATCH, GPIO24 = /OE.
    # PIO can drive the same pins if hardware SPI timing is not wanted.
    u["GPIO20"] += mcu_miso
    u["GPIO21"] += mcu_latch
    u["GPIO22"] += mcu_sclk
    u["GPIO23"] += mcu_mosi
    u["GPIO24"] += mcu_oe_n

    # Status LED on GPIO5 (active high)
    led_net = Net("LED_STATUS")
    u["GPIO5"] += led_net
    led, r = LED("green"), R("1k", "0402")
    led_net & r & Net("LED_STATUS_A") & led["A,K"] & gnd

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    tag(j, "C17502305", "D50P24A4PA00LF", "Amphenol ICC")
    for name, pin in list(METER_OUT.items()) + list(METER_IN.items()):
        j[pin] += meter[name]
    j[METER_GND_PIN] += iso_gnd
    j["SH"] += iso_gnd  # shell / jackscrew holes: meter earth


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
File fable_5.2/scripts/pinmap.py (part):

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for dec, base in ((5, 2), (4, 6), (3, 10), (2, 14), (1, 18), (0, 22)):
    for i, w in enumerate((8, 4, 2, 1)):
        PIN_NET[base + i] = 'DVM_D%d_%d' % (dec, w)
PIN_NET[1] = 'DVM_D6_1'
PIN_NET.update({26: 'DVM_POL_POS', 27: 'DVM_POL_NEG', 28: 'DVM_FN_OUT_A', 29: 'DVM_FN_OUT_B',
                30: 'DVM_RNG_OUT_4', 31: 'DVM_RNG_OUT_2', 32: 'DVM_RNG_OUT_1', 33: 'DVM_PRINT_PULSE',
                34: 'DVM_PRINT_LEVEL', 35: 'DVM_DATA_CAN_CHG', 36: 'DVM_OVERLOAD', 37: 'GND_ISO',
                38: 'DVM_FP_LOCKOUT', 39: 'DVM_SAMPLE_CONTACT', 40: 'DVM_SAMPLE_PULSE', 41: 'DVM_RATIO',
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              46: 'INTEGRATION TIME (1)', 47: 'AUTORANGE', 48: 'RANGE (1)', 49: 'RANGE (2)', 50: 'RANGE (4)'})

# status inputs: SKB 1..36 and the read-back of SKB 38
INPUT_NETS = [PIN_NET[n] for n in range(1, 37)] + ['DVM_FP_LOCKOUT']
# command outputs; PULSE_GATE drives SKB 40 through Q1
OUTPUT_NETS = ['DVM_FP_LOCKOUT', 'DVM_SAMPLE_CONTACT', 'PULSE_GATE', 'DVM_RATIO', 'DVM_FN_CMD_A', 'DVM_FN_CMD_B',
               'DVM_INT_CMD_4', 'DVM_INT_CMD_2', 'DVM_INT_CMD_1', 'DVM_AUTORANGE', 'DVM_RNG_CMD_1', 'DVM_RNG_CMD_2',
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

def default_mcu():
    return {'gpio': {'UART_TX': 0, 'UART_RX': 1, 'SCK': 2, 'MOSI': 3, 'MISO': 4, 'LATCH': 5, 'OEn': 6, 'DRDY': 7,
                     'LED_ACT': 25},
            'gate': {'SCK': 0, 'MOSI': 1, 'LATCH': 2, 'OEn': 3},            # 74LVC125 U4
            'rn1': {'SCK': '1', 'MOSI': '2', 'LATCH': '3', 'OEn': '4'},      # pad of pull-up array RN1
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    """The original assignment: status bit n = SKB pin n+1, command bit k = SKB pin 38+k."""
    groups = {'U10': [PIN_NET[n] for n in range(1, 9)], 'U11': [PIN_NET[n] for n in range(9, 17)],
              'U12': [PIN_NET[n] for n in range(17, 25)], 'U13': [PIN_NET[n] for n in range(25, 33)],
              'U14': [PIN_NET[33], PIN_NET[34], PIN_NET[35], PIN_NET[36], 'DVM_FP_LOCKOUT', 'ID1', 'ID0', 'ID0']}
    pm = {'chain165': list(U165), 'chain595': list(U595), 'inputs': {}, 'pulldown': {}, 'outputs': {}}
    for i, u in enumerate(U165):
        d = list(reversed(groups[u]))           # D0..D7 (D7 is shifted out first)
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    g = m['gpio']
    assert len(set(g.values())) == len(g) == 9 and all(v in GP2PIN for v in g.values()), 'GPIO used twice'
    assert spi_ok(g['SCK'], g['MOSI'], g['MISO']), 'SCK / MOSI / MISO are not pins of one SPI block'
    assert uart_ok(g['UART_TX'], g['UART_RX']), 'UART pins'
    assert sorted(m['gate']) == sorted(DOWN) and sorted(m['gate'].values()) == [0, 1, 2, 3]
    assert sorted(m['chan']) == sorted(DOWN) and sorted(m['chan'].values()) == sorted(DOWN_CH)
    assert sorted(m['rn1']) == sorted(DOWN) and len(set(min(int(v), 9 - int(v)) for v in m['rn1'].values())) == 4
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    of = {node: n for n, v in by.items() for node in v}
    for n in range(1, 51):
        assert of[('J1', str(n))] == PIN_NET[n], 'SKB %d is on net %s' % (n, of[('J1', str(n))])
    exp = {net: {('J1', str(NET_PIN[net]))} for net in set(INPUT_NETS) | set(OUTPUT_NETS) - {'PULSE_GATE'}}
    exp['DVM_SAMPLE_PULSE'] = {('J1', '40'), ('R26', '2'), ('R27', '1')}
    exp['PULSE_GATE'] = {('Q1', '1'), ('R25', '2')}
    for u in U165:
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            arr, k = SER[u][d // 4], d % 4
            exp[net].add((arr, str(k + 1)))
            drdy = ('U8', str(GATES[pm['mcu']['u8']['DRDY']][1]))          # data-ready buffer input
            link = {upin, (arr, str(8 - k))} | ({drdy} if net == 'DVM_PRINT_LEVEL' else set())
            assert by[of[upin]] == link, 'series resistor of %s: %s' % (net, sorted(by[of[upin]]))
    for rn, m in pm['pulldown'].items():
        for pad, net in m.items():
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

def skb(net):
    return 40 if net == 'PULSE_GATE' else NET_PIN[net]


def sch_text_status(pm):
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    u = ((g['UART_TX'] + 4) // 8) % 2
    out += ['', 'Other pins: GPIO%d / GPIO%d = UART%d TX / RX on test pads TP1 / TP2, GPIO%d =' % (
        g['UART_TX'], g['UART_RX'], u, g['LED_ACT']),
        'activity LED, SWD on J3 (Raspberry Pi 3-pin debug connector), BOOTSEL and RESET', 'buttons.']
    return '\n'.join(out)


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
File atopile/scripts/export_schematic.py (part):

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        ("mcu", "swd_header", "status_led"),
        "RP2354A (2 MB in-package flash). Core regulator per RP2350 datasheet:\n"
        "3.3 uH polarity-marked inductor, 4.7 uF CIN/COUT, 33R + 4.7 uF on VREG_AVDD.\n"
        "GPIO16 MISO, GPIO17 LATCH, GPIO18 SCK, GPIO19 MOSI, GPIO20 OE_N, GPIO21 DRDY, GPIO25 status LED.",
    ),
    (
        "isolation",
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        (r"VREG_LX", "power_out"),
        (r"VREG_FB|RUN|SWCLK|XIN", "input"),
        (r"XOUT", "output"),
        (r".*", "bidirectional"),  # GPIO, QSPI, USB_DP/DM, SWDIO
    ],
    "Texas_Instruments_TLV75901PDRVR": [
        (r"IN|GND|EP", "power_in"), (r"OUT", "power_out"), (r"EN|FB", "input"), (r"DNC", "no_connect"),
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        missing = [pad for pad, net in p["pads"].items() if net and pad_count[net] > 1
                   and pad not in {n for n, *_ in sym.pins}]
        if missing:
            print(f"warning: {p['ref']} pads {missing} have no symbol pin", file=sys.stderr)
        comp = {
            **p,
            "sym": sym,
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
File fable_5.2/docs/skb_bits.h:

/* Generated by scripts/pinmap.py from scripts/pinmap.json - do not edit.
 * Bit positions in the 40-bit status stream (bit 0 = first bit shifted out of MISO)
 * and in the 16-bit command word (bit 15 is sent first). */
#pragma once

#define ST_SKB1   5   /* 1 x 10^6 */
#define ST_SKB2   0   /* 8 x 10^5 */
#define ST_SKB3   6   /* 4 x 10^5 */
#define ST_SKB4  13   /* 2 x 10^5 */
#define ST_SKB5  10   /* 1 x 10^5 */
#define ST_SKB6  14   /* 8 x 10^4 */
#define ST_SKB7  20   /* 4 x 10^4 */
#define ST_SKB8  21   /* 2 x 10^4 */
#define ST_SKB9  22   /* 1 x 10^4 */
#define ST_SKB10 23   /* 8 x 10^3 */
#define ST_SKB11 29   /* 4 x 10^3 */
#define ST_SKB12 28   /* 2 x 10^3 */
#define ST_SKB13 30   /* 1 x 10^3 */
#define ST_SKB14 24   /* 8 x 10^2 */
#define ST_SKB15 39   /* 4 x 10^2 */
#define ST_SKB16 36   /* 2 x 10^2 */
#define ST_SKB17 38   /* 1 x 10^2 */
#define ST_SKB18  1   /* 8 x 10^1 */
#define ST_SKB19  7   /* 4 x 10^1 */
#define ST_SKB20 11   /* 2 x 10^1 */
#define ST_SKB21 12   /* 1 x 10^1 */
#define ST_SKB22  8   /* 8 x 10^0 */
#define ST_SKB23 15   /* 4 x 10^0 */
#define ST_SKB24 18   /* 2 x 10^0 */
#define ST_SKB25 19   /* 1 x 10^0 */
#define ST_SKB26 16   /* polarity + */
#define ST_SKB27 17   /* polarity - */
#define ST_SKB28 27   /* function out */
#define ST_SKB29 26   /* function out */
#define ST_SKB30 31   /* range out (4) */
#define ST_SKB31 25   /* range out (2) */
#define ST_SKB32 37   /* range out (1) */
#define ST_SKB33 35   /* PRINT pulse */
#define ST_SKB34  4   /* PRINT level */
#define ST_SKB35  2   /* DATA CAN CHANGE */
#define ST_SKB36  3   /* OVERLOAD */
#define ST_SKB38  9   /* FRONT PANEL LOCKOUT line read-back */
#define ST_MARKER_BIT_32 32   /* always reads 1 */
#define ST_MARKER_BIT_33 33   /* always reads 0 */
#define ST_MARKER_BIT_34 34   /* always reads 0 */

#define CMD_SKB38  0   /* FRONT PANEL LOCKOUT */
#define CMD_SKB40  1   /* SAMPLE pulse (via Q1) */
#define CMD_SKB39  2   /* SAMPLE (contact to 0 V) */
#define CMD_SKB42  3   /* FUNCTION */
#define CMD_SKB43  4   /* FUNCTION */
#define CMD_SKB41  5   /* RATIO */
#define CMD_SKB44  6   /* INTEGRATION TIME (4) */
#define CMD_SKB45  7   /* INTEGRATION TIME (2) */
#define CMD_SKB47  9   /* AUTORANGE */
#define CMD_SKB46 10   /* INTEGRATION TIME (1) */
#define CMD_SKB48 11   /* RANGE (1) */
#define CMD_SKB49 12   /* RANGE (2) */
#define CMD_SKB50 13   /* RANGE (4) */

#define PIN_LATCH     0   /* GPIO number */
#define PIN_OEN       1   /* GPIO number */
#define PIN_SCK       2   /* GPIO number */
#define PIN_MOSI      3   /* GPIO number */
#define PIN_MISO      4   /* GPIO number */
#define PIN_UART_RX   5   /* GPIO number */
#define PIN_UART_TX   8   /* GPIO number */
#define PIN_DRDY     11   /* GPIO number */
#define PIN_LED_ACT  25   /* GPIO number */

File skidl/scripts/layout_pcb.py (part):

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# --- Meter-side registers -------------------------------------------------
# Which register sits in which slot, and which way round, comes from
# scripts/optimise_layout.py (with the pin assignment in the SKiDL design).
# Turned 180 degrees, a register has its clock/latch and supply pins on the
# side away from J1 and the resistor arrays, so the array links stay clear.
SR_Y = 36.6          # bottom row: 4 x 74HCT165
RN_Y = 28.6          # two resistor arrays above each bottom slot
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place("R11", 62.0, 33.0, 0)

# --- USB side ---------------------------------------------------------------
# RP2354A rotated 180 deg: GPIO20-24 (pins 32-36) face the optocouplers,
# the VREG/USB pins (46-54) face the USB connector below, XIN/XOUT/SWD/RUN
# (pins 21-26) face up.
U1 = ("U1",)
place("U1", 95.0, 17.0, 180)
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at("C10", 89.8, 20.55, "h", u1(45))
at("C15", 89.8, 21.6, "h", u1(46))     # VREG_AVDD 4.7u
at("R3", 90.28, 23.1, "v", ("C15", 1), pad_num=2)  # 33R from 3V3
# Right edge (pins 1, 6, 11; GPIO5 = pin 8 status LED exits between them)
at("C5", 100.35, 19.8, "h", u1(1))
at("C17", 100.35, 17.8, "h", u1(6))
at("C6", 100.35, 15.8, "h", u1(11))
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at("R7", 91.9, 9.4, "v")               # RUN pull-up
place("J3", 96.0, 2.6, 90)             # SWD header, along the top edge
place("SW1", 106.0, 22.0, 90)          # BOOTSEL
at("D2", 104.2, 13.0, "h")             # status LED (GPIO5)
at("R9", 104.2, 15.0, "h")
at("D1", 108.5, 13.0, "h")             # 3V3 power LED
at("R2", 108.5, 15.0, "h")
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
